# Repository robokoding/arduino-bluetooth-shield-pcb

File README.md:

View this project on [CADLAB.io](https://cadlab.io/node/889). 

# sumorobot-shield-pcb

<img src="https://lh3.googleusercontent.com/fTmwwAqRyGPrBjHsZT15YX1NfzS3wfSPbC_tjs3XstN7-KH6xNgcncbMV5zCA-tmq7TenIsMVYdql3QMKnN3XMu0jkUxnJVCXWyJofH5LWY-rHjAGG6CyB9k0nP6KTU_ZMHGk81PAgyVVgW5S2n2dYEkUm8CdGcDwA-zARf5z-A-ubhBMVbZU3igCRcgEtIF6Ta1XaOaTLnGr5XTUG59teBGmLF1ol6f102QCiWZQiXe0ahTHqsBYHAdR1WROgVmuZieafkj13USXsEKLqnEbvtbxs_HJ9241scTOW3V2D2IHSW25jnPX44lHCAMWTQpwqQw4lP_PGs-lIGMO_d7DEc19o_5wh_3XONyCR6LNAJReYGXS6oyfRmmx1COFiVkXNUFfzH51QMSaBVlUud-EqRz1R99UXrc4A7zu7Yi9KDe2PUHOeubnBl8PBx1VDV1SZVNwZJST_SSi53b6mer7auuBv82mkosXkyJaHcvrdGb5wctS6IfdziO24HZS7UHQYhVbSf0ejtXy37UBtoYHw3a08CLCojTM5LDusIkpVb8lkST1o6YVW-Dm7BRQ-4XBFS8vKMJ2JS39jmbBD6skP4Xi8briVOezmkAxzvzxcIdVkczzHPb9k4ONmXo6sROj2461QK6xRu2V40z2PSsKhiiSM4i4q5D11Vnj19TxvU=w500-h333-no" alt="sch" height="200px">
<img src="https://lh3.googleusercontent.com/gSWPMYBV_dLu0oRvvOVRaZOyMZZn0yVTpOaDFH5DDjsz7ksmHh2ay3NLqUN_yq7_JKeqfQ06NB_tEY67_auKK1fe7t_xxW4eUWABc9WPw2vDeLPYGpXyaPlxFBCXpKQqaTeeKgQzFd9CfhMvfmQEXk7hwe1b7wPp80tkkTOQmLO-wk1Mg102fub4ewJHTcyjyJGgiqgpZqXrjAdMOJFfd_kKW0dOtRlYB_J7BEyfA_79XtrNhT2NIntn76P8PiHzJxemBV4ymaDup-38UpqVRDpR9TZ6gvDnk24q72Bo_Hrg3GCCWaDAW5RUi8EaGhffLLRBQIz60T2bCYvQYxzGeldcM51UNs7BwakzUOv-rb7jD0B6yBN8Z1KISElqrDn-IIUVVwXRqkdKwpo2-jC-v3h6OcbTj8hUfUWY9eJUxDjLapcnlp7Q8dFIQePG0f2eX91axdxYUR-0207HneJK28fkelcFxhsAgIUA1CxHbsGDCNf970Rio6CP8FwZI2NdTh4BXIbsT7Op_E6lRVNARguA2TDhsSpXqqz7-72K9IssYcUNYrcKUK3lwCokAYewn1TXEt6v3Y-75GH1gFybUoCgoZ0lM5-zgUQvcimdEeTx6tedjGRZ9XOhO4Jyh2kbtz-inb4PKGfyz7S2SJ2cCSku7av1LMO7qBhgXGEOWhI=w500-h333-no" alt="board" height="200px">
<img src="https://lh3.googleusercontent.com/A0n2RX3q-Tk_upcNSsEvOwLb7d9SczSUejGimWpMkSacNFOtjrek5fvgIfAG45xNhorieNqQQ2OfEq4DLLJ6oTdF_3ElSek95DxHM8IDLr8-yvJSF0ggzQFLl6KZvrt7AnXcvCeFahWlaFXnlSWjP4CmDMxFq8XQieR8dypiLPbkmkl8QBMiMWSpSvvvl_xWdX2xFWQVbuj1L89zI_zrzwZje-_BCDvriL2Hm3xqewUXR8moEk7hF9JXLhNkE1ceM9JSeppknnhJrSiCUYp8P-zUd_JfstHCr2hScpNwth2icEQenm4uOQNeby0WFol6DwWACLE9uY_OdvXkH3SlRGXn4LFthSFgzhIsytEMiemqilHcFV0CfTlxrA_SREt4FYUNKfxWN1t1Eg2JIRojWMk2zm_TIYHp_inW5Eh8D-27IVjAoNUWwL8lCDUJFHe9YnamVMLA9JOP7-5KIc8DoHCJvNAzOrluuTN-UBuNgyMRxzjaa7E3IlVvuVEXhP1VNmoLc9J6fYigjprrs5I4WGwbFpFBMD-f1aEpNgjT97_dWkEjFjFKbzgsAUYwrcBAQCpvHNd9hSDv3zl0T6Qv0uacH4DlXHmy-Adr1SPsdnnJUnUKq85uAWMUGc7cAdjAk8qKxm6PHa7qs4EpVMN0gOakk-7ZLSnZ3jIEAn2_w4s=w500-h333-no" alt="steps" height="240px">
<img src="https://lh3.googleusercontent.com/pMbSZCADdvRYmc0ENs9wENhtpcJ2obfGHrNyWCqtZAnLEUuN1VmRBfykACR3QtoLSj6oHUiAfc2B9XxH4QLAtuO63Qr-0JwOAO7nIfb1geezN2BShguTwQOtG-gHLxELjDDtvCyVPR5Vbpd12xsfq1L4GZN_C22VS7w7np2a40ExKNlm9_luKmyr5l5DNNTo4v_IPxnj26hkasN_UzmyvoWauR0xsMssaXz5vEGpXigBpAXDnd1E2RGueWv763V-D8QbS8owIVmpNBQzXWxwLI5lx70INbAXASNmC7gkHaV3HBxr-IbKsOplhetQYoT4lrCwR4KeBDA_DfE5lulGEJJz9dMdUjVk6iV90HNj6IpRJ4w-xQVgsgGGw8dEJcqWof__0O0LVhl_bmvwXeL6PtiNEJiTZosK-ytx6tqDH86EDrUITgT3LOwnmR4HkFda5IsgxOpmbA2KS9JfUqNMYSR0GsWsmYhfkM_YqtfTrEYGVs14yRnZ34YkTUt6MW9wsQRDb__1UN2PY18fo_iyAw2gQ3boBWEAKnSrfYPkNGI0B1Q9qaaXA8KTGF58l8FsmCe5BmwdauNQNddJNiecKkB9ZkI3gcC7dkoJ80GNwLiIZ5SM1a38XfQVp31l5PS8fmUkM8mLuoAauhTh_vNc6QxaH3Oqapr2HyoV0ayzhuY=w500-h333-no" alt="steps" height="240px">
<img src="https://lh3.googleusercontent.com/Mzmpi3k3cAOVtY_cofb7FHn6YMVf5fIyBsCzCZFebN6497LE7LKGVStIRNeISVbl7NGdnJTI3KHZhz4_Ueyi02ZZOOvYXSzIhduTJssHSb05Zur_m5eBl368RbE69pvG-8Uoamq6RhcHExd6hqjEhitcVUtsvJwbg_XPtPgsjQsx9J5VdqNwhitYCsloVt8IOXEZ7fI6EqNtKmDIwhIdUL05kROBArg9BvHWDIXrp4yJHZJlYhzdOUmgh8kgVCEGlXo2KL5Qhdkv3kp1a8brTNN7rVLrHcoaiBIvHtpKwU-aG7lZfawHM5Wg3ol1F-eqlU9O93KxoNhbyHr_9tHTt0cdh14HL3t8tSlHGF2Jyfj2j0dXr-b1Tpk7mEptWw46TPptpIlQ14_mxvzYWLEGaTcvttzb9GA1JJ3kYWOpcynApCX_kT09yAjc6IhGGlMk-9HttkknFgscK4BZz49kKa9zMXbNHtO6hre2ZqvZsExKwiZwK3vL_Pefus037-qYlYVFRHN0l84CvuWoSv4eCoZrCFcsb2mmxEcUacZhCcs51o3wtBm0KFoPZeEuu2SMu0q8GW3NuDglzKR0C6kKAatl8bppctp3sOeukDHhfzRUPsUOnVSc4iSgPMAlR7sDtvXVgFxAuYkw76nfgmppe2B1E9lvOryEXBUqmYhwkvM=w500-h333-no" alt="steps" height="240px">
<img src="https://lh3.googleusercontent.com/KAMJBVOLPEiPGtxhSHbksUNNfZWr21kFEriczpTQUVpMiKqgRjQ2zEg_I8y7_QAey9u-DUIcjSVapeUwKoTNr8PoEbwIRwXP9oW9wZcy4X7697Lx-SXMDEdAH2_EgBdYgExNobzk6QPYx1gnaKCGb3puVw3PzrcWAiSqfTJr_jZQUp4dw5pNbIofotcq8DGp6qx-CH3QM72PZkABQexFy5gaUIoefr48V0-dANUUEwQGwYk7SeJJUqX8ntBRhMeoBoQL1plfv95fRppcISkLjqwn93X47dhhH69YYZ-J6nBbht7CtsjRrB18gO_qh1z_dsArTEhjG-lxnyJb3HFWUV52M_LdR6JreZ0_BlxTWAiNor_qfeIOY02YkVpIrdIBbxUjd7chzsolB1iIv_yQX4MkocnkEN9IptNsHCIYNrIzlcl90dX2JLh_0i2P19G37J3A0ssXyCOPNN6DFT3LvvlXqXKmlf-gQ3XIf6hooVLcKGw1H0WxpUzXpKuVou1EODzi7q7l4X7zYShSwVIHlUsLsmLiUH1CwzNINSTvHezLI8Coxkn6zLycjJ6v7RlGJQEV2Uk4ouv9yu5v3blv7xG75V8u6M0iiXNXqLnhESTihsu99_PpuaGfflSydIzoK6nqJ6hlYziQ1aExjTudjSYHfKq8ssiKNSz57hDzF3A=w500-h333-no" alt="steps" height="240px">
<img src="https://lh3.googleusercontent.com/TpL-ZBw1egrHlMzpm606_HK8rS254JicbxKOjHnu-9a3L-pmRBa2lxEkrhJCK5ekLqw8N3RAvYcmV313upHTkjccPvR4DEncFY-Ac8Z97dRbZmf0_W1HEZOQU_-2HCwbpiE3HbRM1_5RdGliOFI4XzPSRTxvhyiGDLYWH06YGDAWK5bd_YOL9LztABl6MxOX0rVYAFcjzQfXbvkE844_CN3DQmhsZohk-m7D3Ezp_OVngsUyycBrHL7JvSItDJq9RSnCmFQdsAtYr1hBgr9byhd21pDOBpmUdGF6-Em7BT_OSRJqlATsxTw9qViT5XmNymy2tqvpciN9FMmkmPgufcBPdGLqDwSF4s8ruqO1aRH-_J_C-Zkm2xs_b459fe3Y892cJfVInA72rMokTOAFBqvlyT08VlCiQUzmqzT4aFG3nK7ChjUV_K5IVdj2ZBvBsUB02Pmf4mO3TXs3Qo1V2ZaayuFTg3Hg-yz-z7NUo3phNzvRSS1xyzThzA7Qr-QjHcjJ1TGu-v_08zXCBj74Aq74fdwjTQ24JbdZYm5k64A6QU7HXvjlk3IyiUR3y_XXbWNIAvFp-H-wHFFhcPBgUXklXzibYNQyhJdw1-LSBqin3clwa907MeO79EcrtgAAmnytmrttF7rfePkrGAcjNlchRWA3kiuhcW6g6TdQE_s=w500-h333-no" alt="steps" height="240px">
<img src="https://lh3.googleusercontent.com/hBxpA7Br7P0n9i1vf-ijPuUHvhQL2R2jjjn94xsbul5iWPPqi1pzFgC27GY7274DwZUnSG74NRy-mm1c9ftv7z0H36PVfFQZGbKpV5vPSqBkq-kYSpYXfpXnv_-3RbhSnYL530VbrW7fRzWPE3s9Kql2jX9jbwj8HJ4cj7Qiiwo8O-lHIH1m17rSzo9e7NIWSSpZ-1G-ggf0ptE6NlODX_rS2WYI52P1grsoI9BAOJidVAS_88KjBCqIXLzhGIE7G-p9oRe6ZrPw9RyBcoM6a5RRcNKZ4SR8M9WNZE3zKKphb0FM6RItMX35sRQ0ht3wtiTKfkUJwAOLzY6HP6rilIeWO933S3zbj_37mGCUAvQxIsqzvJQtzLWtXovKDImjJk_e9T32WzaRz-POu9CBeZt1_POkDvyGipLO7hePeHb49WwmkyEVwuhJIn65yLCGUTyqG3ZHwGbOKY6fGmWEphFrmfdhftBKmD9UUlpWrYSBxdUe2oIIDox8qvIqQ2zuvtWaHgi9dsiwi_RJhwbTapSLrKMXsdOLc2oT_of1ezsv6uzu-Mnq3AS6y5j8JR6eR_GwHoo2nL0nPvJTPUCh864Hx7nnEMY742abjSpiBkG9sq1Ml5lNSxn21R9ncdbDJBpauRsQj1TowYlTx7u64n0zLCz3R9U4hVmikulhDoE=w500-h333-no" alt="steps" height="240px">
<img src="https://lh3.googleusercontent.com/sqtV61k0n3Vhc6lmeMkyT5uddaJ2eq9T2uR--S0sBhjyMnPUiAzd-wt_gYIQDy649wAUn2NEttyknFN2nPcOrTWoI0sod2iDI0ZNlDMYJkv1nmdCTMd4NUgjrUrd-uK_sQcLsgi0W00zIrzMORKDg4tYqWaFGgM_99W_2W5zbMccQab_gyRXDG2ea_afktXh4dQefScI4vKzQ003O4aiUihiWN6mNAU8JvcVi76mNw1RgrM0lM8MVrKuDg3y0_5yKnxE060Mciv7eSOiwgW_mDAb4NfE7wyW4aD7f06IyGNHPEH52o6UjzAwOq_paUTs2rVmrZYbBKrqlWdrruLPas9osFm1ejmBaayGV8LOr9wDg28_sAY_l5J7E3nRZLL4lcwoKedMKfMTDsO4cB4otyK3aZCEIAop5oYL7zGZfJgW7zroQpNnh-GIrbzXV8tEKFkZuxhJu9DtedkN6ICjcm-gajlKHkwWoLuB6XwXaT8iC_j17iIRkvkrrAOOvEM5UY3XE1KheeV-h3mKJjjcM2485IHeDe9MLU2N6DEHFd2IFstDheqlT6EUE5J_kP1FxZPyynCDYTTEvJrMvSDFFvuWZ_zH55M7nI9g8tnlvp3JL3ODDVOtEzqrGljqfFFo2iP6niz0Pa5v0HKhdB1445MrwkZ6-Z4sqLxwwXjB9a8=w500-h333-no" alt="steps" height="240px">
<img src="https://lh3.googleusercontent.com/1OFcT_GURgtJQpp01EsRz12DKud34eFzkMIPJCCjaUONKjRVUqrC8owTuNvgwedMmkuRxZfnsZG0VzeZpfVI860Ww3fj6vxTeVuL6dqVczMyI0_GnQdl1KgJDfoJAB2Uhzh16LlCsDXhpHZwIcP8K5MMfL7tEHVEFljByMlg-mhUPoBS780e103fALzuT5IZG-oBFzcwdsYO90FBr7tSWm3ATSX6EaHWGpOSGswDl7ZYSRpQVRD26J_1ELIPcuZMWcHgiitPKste_EHCS7KGPeIARvyvuqQtRJXI9k0JHz8pNGiKAwRBN3nslM0JvcU5pHf9miIlQtoLtKleQIiPNX3d9iTfw0Q88ZbYjf0mtjO-Qf1rC_oEZ8TrNcFj-tr7xSZEdcCRBMX6Q0puNbAB3sQXrPCxKkImQS9Szxi4cdBT07M_Xvsq6rrpnBqfVa3NAf6cSQGZqSR1RtxKXnRzqOGl7l4l3oLzT6wy8n2vxjlSHnuvx1NndO2MJcs_dWxyj3Asy1BZkaZzlZrCUeUfsjrt5qYuwmmqiwoezyAa8l2UOIBd--08GJZLomozkRxMKpRgVUUruT2pW4MhXnekimI4KDdJ6mFulVkWyNO8-CROCBOqheq_dhZkweDqA3f4PXkyrrWTlh7CiHm_gJFD11V7wnPIj2WobrdFE9DrVMo=w500-h333-no" alt="steps" height="240px">
<img src="https://lh3.googleusercontent.com/b3gXWx2SfTD2bc-8tWj3GJCRONKzjnPxY-KBO_m1n8JM8aM7JSVCyPvJ4HzNj8j4rIDIuynDOCHZEdarxLXjtDUxqJqV2G-0uN9O74H51bJlozrFRd6RbMtP3h_ItY7yRpnrkIm7E9KY0j18-AIYaHuwEUizqRkjDJ11Kcn4F6cdwn86GDJEEN6s00NSxwZ1BmgNJ3YAeqOkHryHwmJQzjLyfUIo8mO35if4gjr-4f6cCm3rRZo0EICxSmMqVvzk4ebVZcWJIdKxZ09ZI6EK9avKyKHh5uRHblSHtvfuUt3k25qNBsNt4IXfBnj2Xw0Pf6Eewf_8MbKZCTBrNWvJ6ub4QaU3wI97iy_laLOLTyVMOlEdCnWbTNip9GKLNrVZL0ZUZI63bMNcSL_TXez34fiZzK6YN6774uISARiJZ71wUdRN19mRkd1Hzka0AjPd8HHPAOxMzvlsPN31d8xhHZbJ5yREsxfruXw_J5Wx9sBMu5s6OzoIEqILqfvYIMr9P9HSZwOJgo_xBgucf1G6zy9vkdLNf9_u6TmbLNp26IUvxO9Nm2js5oNNfakLTDhk2nvpMtHNIJfms9oZ5G764RN0cy8BgCEGUwJPbnMll19rlaFAf53D9_cgkcjYQShp60w3eRaG-PV3P9DrtnH2pIEOJt3fxNxhS4subLR9b3I=w500-h333-no" alt="steps" height="240px">
<img src="https://lh3.googleusercontent.com/niF6IIVR80dQME8Ey1LvzJthr830BqPslgQ4GN3q4vd-kzgKHSBMkObYACPL8xqJNdbsRmFhYgg5fXn01RpT7Q4VX1VsLGAYNbPvDBzNSTLISghnXICCZeL--JADQl11qxBUyZBJzoPrYlGM2uPJisMdeMhMqDYjhAjlGGhXT3GzCY8_Nf7FIKs5ASxxIBDsAO30XeyiH9laujJnFHIS9Sn_ErXdROLZRU_b33r7Pr19UQ7aNlLMMoft3Xo3AqKzNMs4CtDiWr4MDLtdSDyJFZDCg8CXEyLvsrT7AJ-Kl5AagdMwjbVYizC1gcK4vnk2F5SuiIxLSNfjFxxoJFhmI1Y14d_D1RmEerCWZS8TRlSTpO2udMQkWlsXrkAUw8zP8S9MtCUE56X_3DonbY-Egvsw5Qp_2Ok91T8DgRSk0LM55M5Bfn6YDjs1SH6H8SSofhLbXzAwrhY8icl_hfWrjGMMIXvD64CpwDIowX4qLGBgYFYt_YoqlRM_Y0EoH2ZA3zkXMUuE2mGWLvsBGD4CYZEEkoDkgJe6ApBP82nJjf5GYy0sOMAgdOGCkSq7mSvQRZ8sZlAelDP9EZ1VKxcbN6zi-bFFAbLK9Q-AnAfJaH9Z4X_qFj3RXIVRkFg9HE2aGfqkjZ8-t_-eagZQBAqew_RHL8c8hQ-BVQu9x9vODoE=w500-h333-no" alt="steps" height="240px">
<img src="https://lh3.googleusercontent.com/3fWoJ3eG_F5jxeiGZlos3DI3WcORRohD-eza2SIjVstscrOphfx8qdmI6Fhr3foXBzu-U6-5o5EJzS9BNMupVNSf7ClYyK8TX4AxdO46vBvmdgQ9ILIpCp6NkJDIyqaXznAnnXPqUuDquW8E_z82b3naHgcOKDQxodayA_mkvkyKTQ3nwNp6-Wd-TmrggsMsEXL2UMqwPswlZC9MaGqdOvLVGv4dBmeWDdGOTr3De14yyiF-59YUYpXuwqiEKDUdfIG--KPsWLcCmZ05TL7GIHCVPEj4BIGPNTzWgbSQX0bo3S3RjBMJFPfXT9eolfq-PKPjXxmXUfYOBkoMM1TO_89etM_GbtvhhSivPx5arWnhW0Dx3qkX90b4S1Nj0PqJxf3CAi_iB7gVPtiu0hQLdquOEWSqomJZTKoKHg7cYWRdadeo75sAOJQ0LmD0wI3rPi2DkPk9K4sFMy8Iq0ZMRIEAxvtWs4_0YYqG9Zcx5Z3C50NW4z2319lhak3AI7mdwnDWq1J9SLO_WyFoAv3fxJXvYBcbkJBJo0ahFIrvFK1-B0g7fHVyHYM6ksNd47ROKOUWp1tsPmWeTgh6bf4W75RAeg_JgUoTZ5OqNJ-4FwxWa0g_RZaNIdBu8iqRaWZZhTqs0wr7de-ahk8J3U4VSY0dMlrFbfs4hFA2U912eOw=w500-h333-no" alt="steps" height="240px">
<img src="https://lh3.googleusercontent.com/JFwPLg10FBvNmtlCt7pxDTylHI33aRbeqaRLOeu5TAfTy9t0Q3eaa91MP6EPemtr7uzlu9ezU1P7tj4KNzeGfU5oskvEx3DCOS9bMZELLS0WQ9L6YGW-vVMbDPjTPxFV07o3zpUOI8VAjv1NG2Hirag4jxKxMRB90Z54FfoZCR08Bh4fB9Y_O-eobfRa8B_KK8cuZpyn6SfHE7pBJQsULmog4j5XcHdZrg48R5T8lESzC2Cp8giLHFxqh9Plf3ulWJd1JEgGax4aWq1q4yc4ZxTceWsgHElPYDk7b3tuhsmR5H5-MsWwteR75KGrCVauFulAnU6ztL-Pu9Sh7QcG6KsJJjlU1rw80YrNZ7v10iolTcnZ-XiX8mTjnpsWPaZmw1GuBMnaDoKV_RkUK5_dO2TUb2BcaCIsqZnFXmTmp0h8Xp_s_zI_wIlwEKWunUFrAyehOR4efwmAEqqbM2SddVbMDDH3A-z89nuFhw91dm6GRNPNeLZM28w5ThKPkqijHGXxZOpYEUVyLeZy8BqRMCpXSBP2bBb7m6do1iSUzaezQRAbPSMEaysej-hbdrii7w1oUJKHTlBGbSyB54sUY4Yg5QrivYW_bL-gQPVqDwubUatMlJ42b2wuAndigarbWjV6TCgVvrl1uqCyrHYu9Al5xJG5SbqiAedTKbLnKN8=w640-h427-no" alt="steps" height="240px">

Sumorobot shield with HC-05 Bluetooth module. The HC-06, HC-07, HC-08, HC-09 and HM-10 modules have also a compatible pinout, except for the status LED.

# Credits ^_^
https://github.com/sparkfun/SparkFun-Eagle-Libraries
http://wiki.pinguino.cc/index.php/SPP_Bluetooth_Modules

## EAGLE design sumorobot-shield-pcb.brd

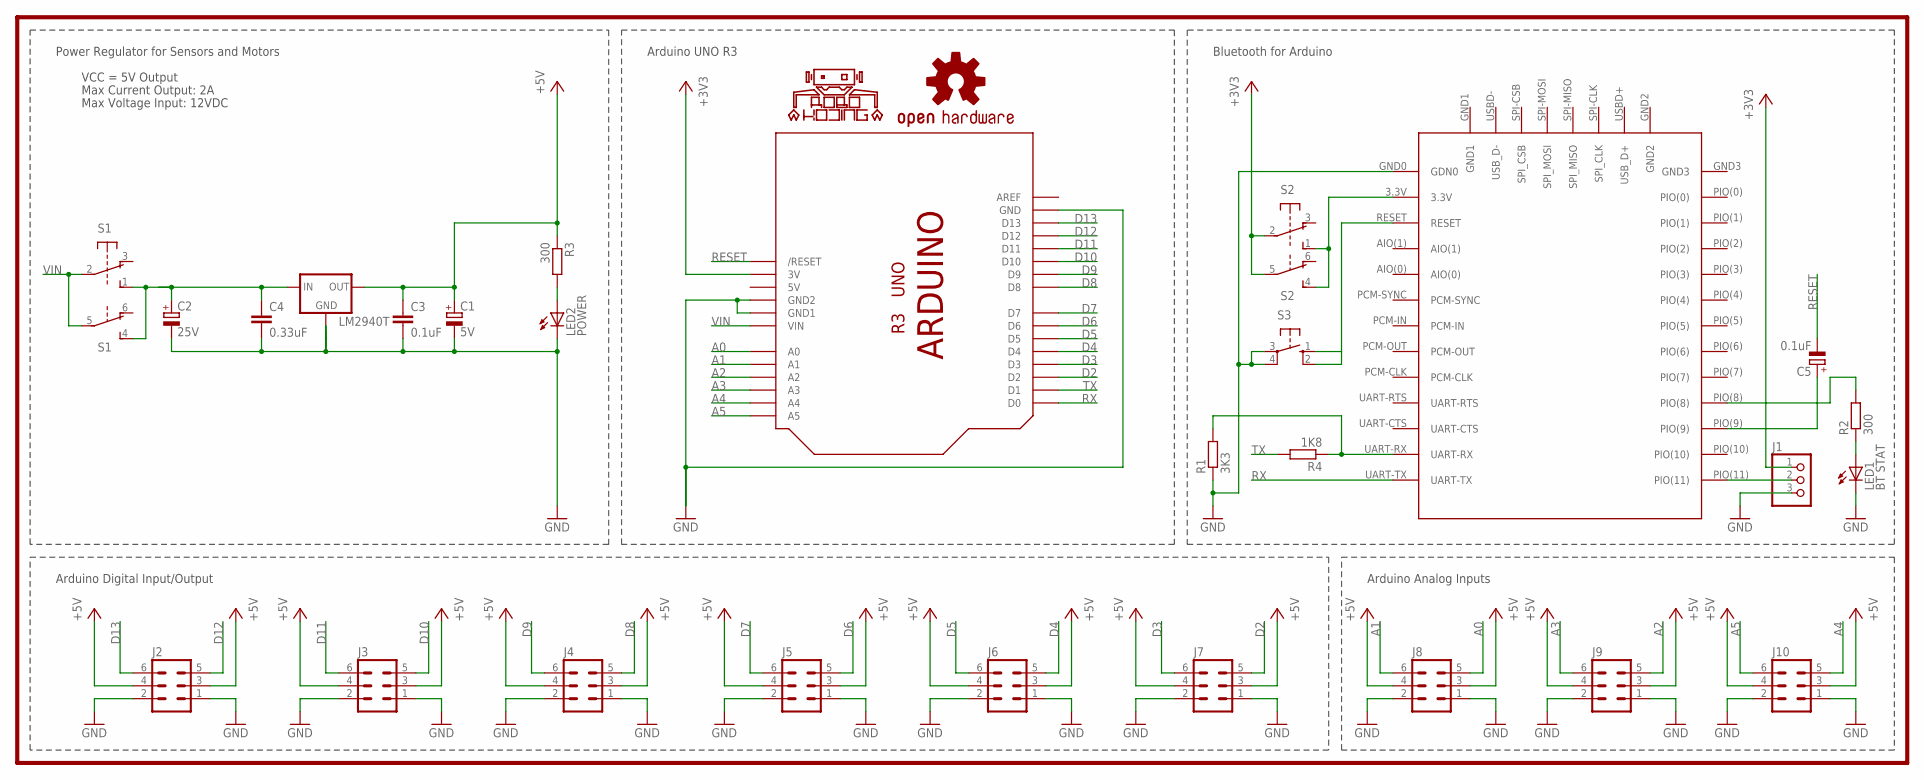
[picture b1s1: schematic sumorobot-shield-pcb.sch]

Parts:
BLUETOOTH: MODULE; SKU_80711
C1: 5V; E3,5-8
C2: 25V; E2,5-7
C3: 0.1uF; C025-024X044
C4: 0.33uF; C025-024X044
C5: 0.1uF; E5-4
J1: PINHD-1X3; 1X03
J2, J3, J4, J5, J6, J7, J8, J9, J10: MA03-2
LED1: BT STAT; LED5MM
LED2: POWER; LED5MM
LM2940T: 78XXL
LOGO1: ROBOKODING-LOGOL; ROBOKODING-LOGO-L
LOGO2: OSHW-LOGOL; OSHW-LOGO-L
R1: 3K3; 0204/7
R2, R3: 300; 0204/7
R4: 1K8; 0204/7
S1, S2: 9077-2
S3: 10-XX; B3F-10XX
U$1: SUMOINO-SHIELD

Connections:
5V: U$1.5V
+3V3: J1.1, S2.2, S2.5, U$1.3V
A0: J8.5, U$1.A0
A1: J8.6, U$1.A1
A2: J9.5, U$1.A2
A3: J9.6, U$1.A3
A4: J10.5, U$1.A4
A5: J10.6, U$1.A5
D2: J7.5, U$1.D2
D3: J7.6, U$1.D3
D4: J6.5, U$1.D4
D5: J6.6, U$1.D5
D6: J5.5, U$1.D6
D7: J5.6, U$1.D7
D8: J4.5, U$1.D8
D9: J4.6, U$1.D9
D10: J3.5, U$1.D10
D11: J3.6, U$1.D11
D12: J2.5, U$1.D12
D13: J2.6, U$1.D13
GND: BLUETOOTH.GND0 (GDN0), C1.-, C2.-, C3.2, C4.2, J1.3, J2.1, J2.2, J3.1, J3.2, J4.1, J4.2, J5.1, J5.2, J6.1, J6.2, J7.1, J7.2, J8.1, J8.2, J9.1, J9.2, J10.1, J10.2, LED1.K (C), LED2.K (C), LM2940T.GND, R1.1, S3.3, S3.4 (P1), U$1.GND, U$1.GND1, U$1.GND2
unnamed: BLUETOOTH.3.3V, S2.1 (S), S2.4 (S)
unnamed: BLUETOOTH.RESET, S3.1 (S), S3.2 (S1)
unnamed: LED2.A, R3.2
unnamed: BLUETOOTH.PIO(9), C5.+
unnamed: C2.+, C4.1, LM2940T.IN, S1.1 (S), S1.4 (S)
unnamed: BLUETOOTH.PIO(8), R2.2
unnamed: BLUETOOTH.UART-RX, R1.2, R4.1
unnamed: LED1.A, R2.1
unnamed: BLUETOOTH.PIO(11), J1.2
RESET: C5.-, U$1.RESET (/RESET)
RX: BLUETOOTH.UART-TX, U$1.D0
TX: R4.2, U$1.D1
VCC: C1.+, C3.1, J2.3, J2.4, J3.3, J3.4, J4.3, J4.4, J5.3, J5.4, J6.3, J6.4, J7.3, J7.4, J8.3, J8.4, J9.3, J9.4, J10.3, J10.4, LM2940T.OUT, R3.1
VIN: S1.2, S1.5, U$1.VIN

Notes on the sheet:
Power Regulator for Sensors and Motors
Arduino Analog Inputs
Arduino Digital Input/Output
Bluetooth for Arduino
Arduino UNO R3
VCC = 5V Output
Max Voltage Input: 12VDC
Max Current Output: 2A

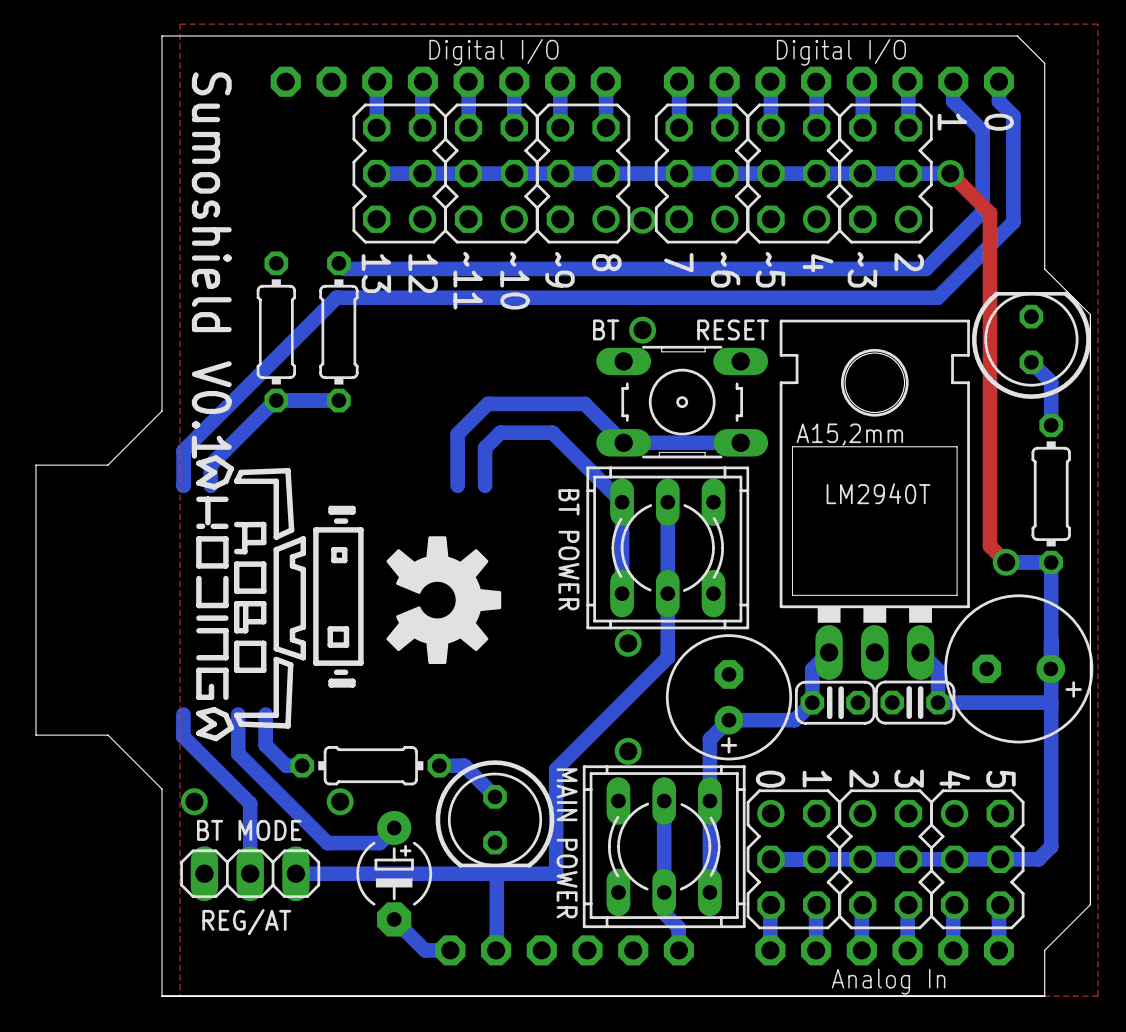
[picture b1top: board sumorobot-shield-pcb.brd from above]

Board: 2 copper layers, 58.6 x 53.3 mm, 29 parts (1 on the bottom side), 34 nets.

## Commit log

2015-01-29 updated schematics and board + renaming
2015-07-09 updated sumorobot shield
2018-04-16 Backlink to CADLAB.io has been added.
2019-02-11 move label

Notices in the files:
parts and their libraries:
SparkFun-Aesthetics: Licensing: Creative Commons ShareAlike 4.0 International - https://creativecommons.org/licenses/by-sa/4.0
